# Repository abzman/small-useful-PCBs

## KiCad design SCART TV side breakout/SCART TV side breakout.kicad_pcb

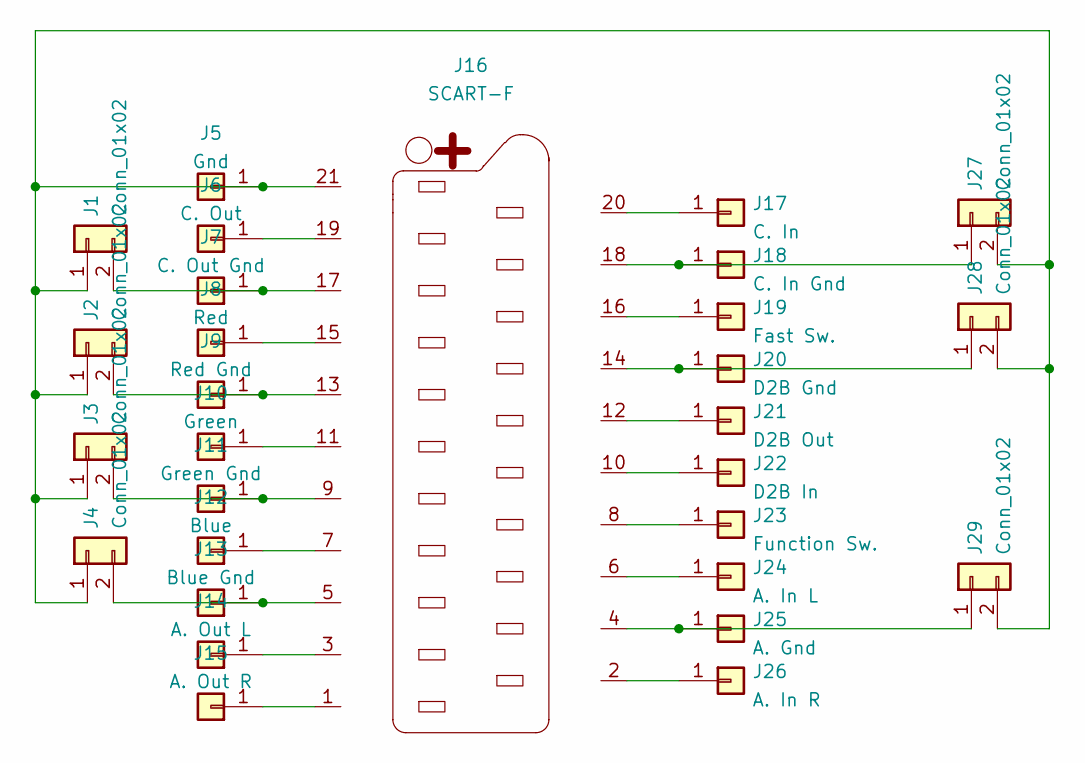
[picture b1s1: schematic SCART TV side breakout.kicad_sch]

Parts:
J1, J2, J3, J4, J27, J28, J29: Conn_01x02; SolderJumper-2_P1.3mm_Open_RoundedPad1.0x1.5mm
J5: Gnd; PinHeader_1x01_P2.54mm_Vertical
J6: C. Out; PinHeader_1x01_P2.54mm_Vertical
J7: C. Out Gnd; PinHeader_1x01_P2.54mm_Vertical
J8: Red; PinHeader_1x01_P2.54mm_Vertical
J9: Red Gnd; PinHeader_1x01_P2.54mm_Vertical
J10: Green; PinHeader_1x01_P2.54mm_Vertical
J11: Green Gnd; PinHeader_1x01_P2.54mm_Vertical
J12: Blue; PinHeader_1x01_P2.54mm_Vertical
J13: Blue Gnd; PinHeader_1x01_P2.54mm_Vertical
J14: A. Out L; PinHeader_1x01_P2.54mm_Vertical
J15: A. Out R; PinHeader_1x01_P2.54mm_Vertical
J16: SCART-F
J17: C. In; PinHeader_1x01_P2.54mm_Vertical
J18: C. In Gnd; PinHeader_1x01_P2.54mm_Vertical
J19: Fast Sw.; PinHeader_1x01_P2.54mm_Vertical
J20: D2B Gnd; PinHeader_1x01_P2.54mm_Vertical
J21: D2B Out; PinHeader_1x01_P2.54mm_Vertical
J22: D2B In; PinHeader_1x01_P2.54mm_Vertical
J23: Function Sw.; PinHeader_1x01_P2.54mm_Vertical
J24: A. In L; PinHeader_1x01_P2.54mm_Vertical
J25: A. Gnd; PinHeader_1x01_P2.54mm_Vertical
J26: A. In R; PinHeader_1x01_P2.54mm_Vertical

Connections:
unnamed: J1.1, J2.1, J3.1, J4.1, J5.1, J16.21, J27.2, J28.2, J29.2
unnamed: J1.2, J7.1, J16.17
unnamed: J10.1, J16.11
unnamed: J3.2, J11.1, J16.9
unnamed: J12.1, J16.7
unnamed: J4.2, J13.1, J16.5
unnamed: J14.1, J16.3
unnamed: J15.1, J16.1
unnamed: J16.2, J26.1
unnamed: J16.4, J25.1, J29.1
unnamed: J16.6, J24.1
unnamed: J16.8, J23.1
unnamed: J16.10, J22.1
unnamed: J16.12, J21.1
unnamed: J2.2, J9.1, J16.13
unnamed: J16.14, J20.1, J28.1
unnamed: J8.1, J16.15
unnamed: J16.16, J19.1
unnamed: J16.18, J18.1, J27.1
unnamed: J6.1, J16.19
unnamed: J16.20, J17.1

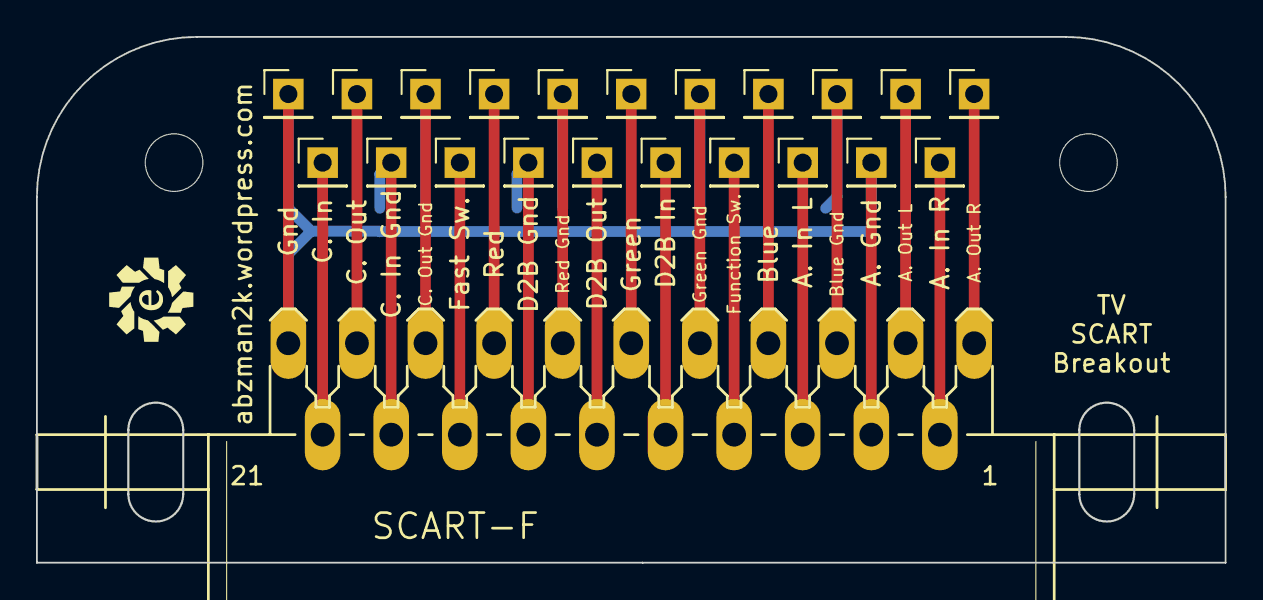
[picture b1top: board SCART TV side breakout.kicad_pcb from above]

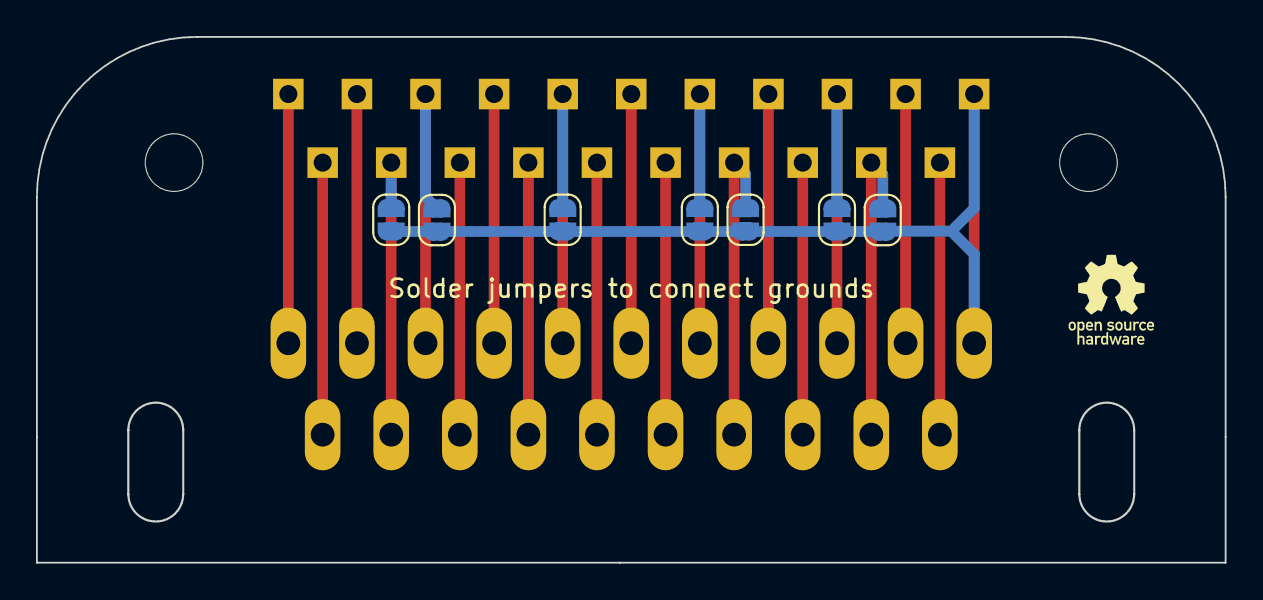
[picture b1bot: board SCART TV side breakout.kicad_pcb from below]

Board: 2 copper layers, 66.0 x 29.2 mm, 29 parts (7 on the bottom side), 21 nets.

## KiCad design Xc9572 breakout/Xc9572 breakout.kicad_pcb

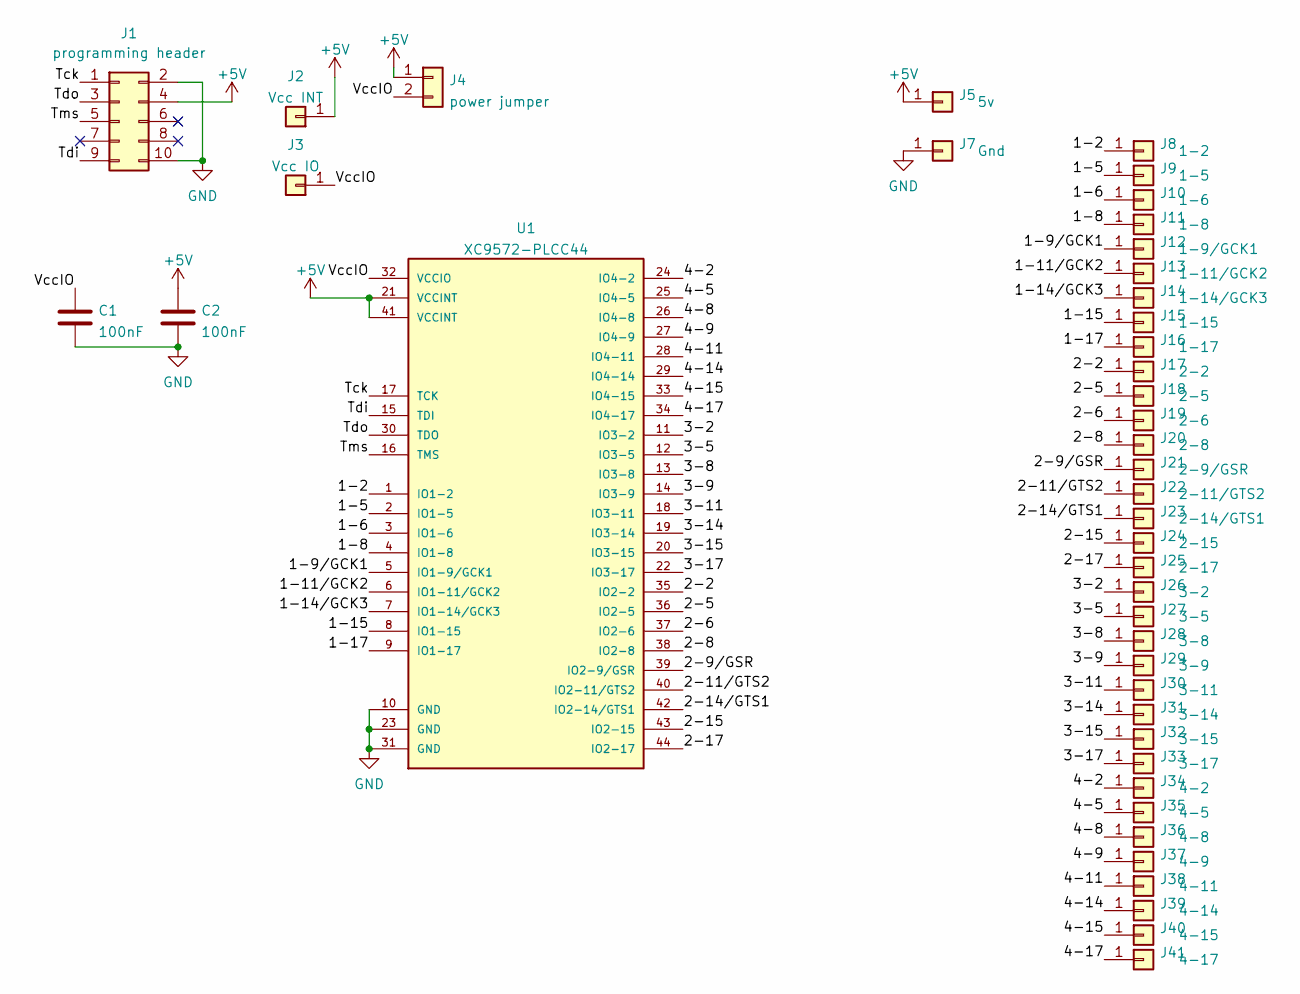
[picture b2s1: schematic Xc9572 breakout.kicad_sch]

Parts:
C1, C2: 100nF; C_0603_1608Metric
J1: programming header; PinHeader_2x05_P2.54mm_Vertical
J2: Vcc INT; PinHeader_1x01_P2.54mm_Vertical
J3: Vcc IO; PinHeader_1x01_P2.54mm_Vertical
J4: power jumper; PinHeader_1x02_P2.54mm_Vertical
J5: 5v; PinHeader_1x01_P2.54mm_Vertical
J7: Gnd; PinHeader_1x01_P2.54mm_Vertical
J8: 1-2; PinHeader_1x01_P2.54mm_Vertical
J9: 1-5; PinHeader_1x01_P2.54mm_Vertical
J10: 1-6; PinHeader_1x01_P2.54mm_Vertical
J11: 1-8; PinHeader_1x01_P2.54mm_Vertical
J12: 1-9/GCK1; PinHeader_1x01_P2.54mm_Vertical
J13: 1-11/GCK2; PinHeader_1x01_P2.54mm_Vertical
J14: 1-14/GCK3; PinHeader_1x01_P2.54mm_Vertical
J15: 1-15; PinHeader_1x01_P2.54mm_Vertical
J16: 1-17; PinHeader_1x01_P2.54mm_Vertical
J17: 2-2; PinHeader_1x01_P2.54mm_Vertical
J18: 2-5; PinHeader_1x01_P2.54mm_Vertical
J19: 2-6; PinHeader_1x01_P2.54mm_Vertical
J20: 2-8; PinHeader_1x01_P2.54mm_Vertical
J21: 2-9/GSR; PinHeader_1x01_P2.54mm_Vertical
J22: 2-11/GTS2; PinHeader_1x01_P2.54mm_Vertical
J23: 2-14/GTS1; PinHeader_1x01_P2.54mm_Vertical
J24: 2-15; PinHeader_1x01_P2.54mm_Vertical
J25: 2-17; PinHeader_1x01_P2.54mm_Vertical
J26: 3-2; PinHeader_1x01_P2.54mm_Vertical
J27: 3-5; PinHeader_1x01_P2.54mm_Vertical
J28: 3-8; PinHeader_1x01_P2.54mm_Vertical
J29: 3-9; PinHeader_1x01_P2.54mm_Vertical
J30: 3-11; PinHeader_1x01_P2.54mm_Vertical
J31: 3-14; PinHeader_1x01_P2.54mm_Vertical
J32: 3-15; PinHeader_1x01_P2.54mm_Vertical
J33: 3-17; PinHeader_1x01_P2.54mm_Vertical
J34: 4-2; PinHeader_1x01_P2.54mm_Vertical
J35: 4-5; PinHeader_1x01_P2.54mm_Vertical
J36: 4-8; PinHeader_1x01_P2.54mm_Vertical
J37: 4-9; PinHeader_1x01_P2.54mm_Vertical
J38: 4-11; PinHeader_1x01_P2.54mm_Vertical
J39: 4-14; PinHeader_1x01_P2.54mm_Vertical
J40: 4-15; PinHeader_1x01_P2.54mm_Vertical
J41: 4-17; PinHeader_1x01_P2.54mm_Vertical
U1: XC9572-PLCC44; PLCC-44

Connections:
+5V: C2.1, J1.4, J2.1, J4.1, J5.1, U1.21 (VCCINT), U1.41 (VCCINT)
/1-2: J8.1, U1.1 (IO1-2)
/1-5: J9.1, U1.2 (IO1-5)
/1-6: J10.1, U1.3 (IO1-6)
/1-8: J11.1, U1.4 (IO1-8)
/1-9/GCK1: J12.1, U1.5 (IO1-9/GCK1)
/1-11/GCK2: J13.1, U1.6 (IO1-11/GCK2)
/1-14/GCK3: J14.1, U1.7 (IO1-14/GCK3)
/1-15: J15.1, U1.8 (IO1-15)
/1-17: J16.1, U1.9 (IO1-17)
/2-2: J17.1, U1.35 (IO2-2)
/2-5: J18.1, U1.36 (IO2-5)
/2-6: J19.1, U1.37 (IO2-6)
/2-8: J20.1, U1.38 (IO2-8)
/2-9/GSR: J21.1, U1.39 (IO2-9/GSR)
/2-11/GTS2: J22.1, U1.40 (IO2-11/GTS2)
/2-14/GTS1: J23.1, U1.42 (IO2-14/GTS1)
/2-15: J24.1, U1.43 (IO2-15)
/2-17: J25.1, U1.44 (IO2-17)
/3-2: J26.1, U1.11 (IO3-2)
/3-5: J27.1, U1.12 (IO3-5)
/3-8: J28.1, U1.13 (IO3-8)
/3-9: J29.1, U1.14 (IO3-9)
/3-11: J30.1, U1.18 (IO3-11)
/3-14: J31.1, U1.19 (IO3-14)
/3-15: J32.1, U1.20 (IO3-15)
/3-17: J33.1, U1.22 (IO3-17)
/4-2: J34.1, U1.24 (IO4-2)
/4-5: J35.1, U1.25 (IO4-5)
/4-8: J36.1, U1.26 (IO4-8)
/4-9: J37.1, U1.27 (IO4-9)
/4-11: J38.1, U1.28 (IO4-11)
/4-14: J39.1, U1.29 (IO4-14)
/4-15: J40.1, U1.33 (IO4-15)
/4-17: J41.1, U1.34 (IO4-17)
/Tck: J1.1, U1.17 (TCK)
/Tdi: J1.9, U1.15 (TDI)
/Tdo: J1.3, U1.30 (TDO)
/Tms: J1.5, U1.16 (TMS)
/VccIO: C1.1, J3.1, J4.2, U1.32 (VCCIO)
GND: C1.2, C2.2, J1.2, J1.10, J7.1, U1.10 (GND), U1.23 (GND), U1.31 (GND)

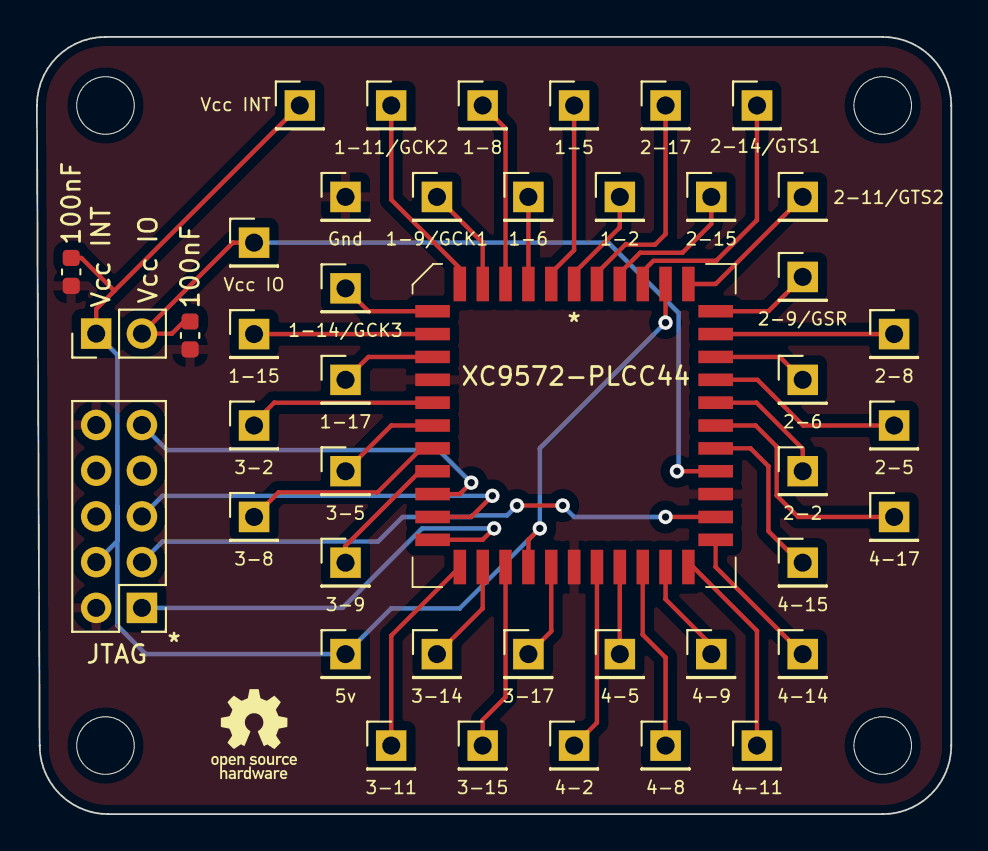
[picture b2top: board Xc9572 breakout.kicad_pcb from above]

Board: 2 copper layers, 50.8 x 43.2 mm, 43 parts (0 on the bottom side), 41 nets.

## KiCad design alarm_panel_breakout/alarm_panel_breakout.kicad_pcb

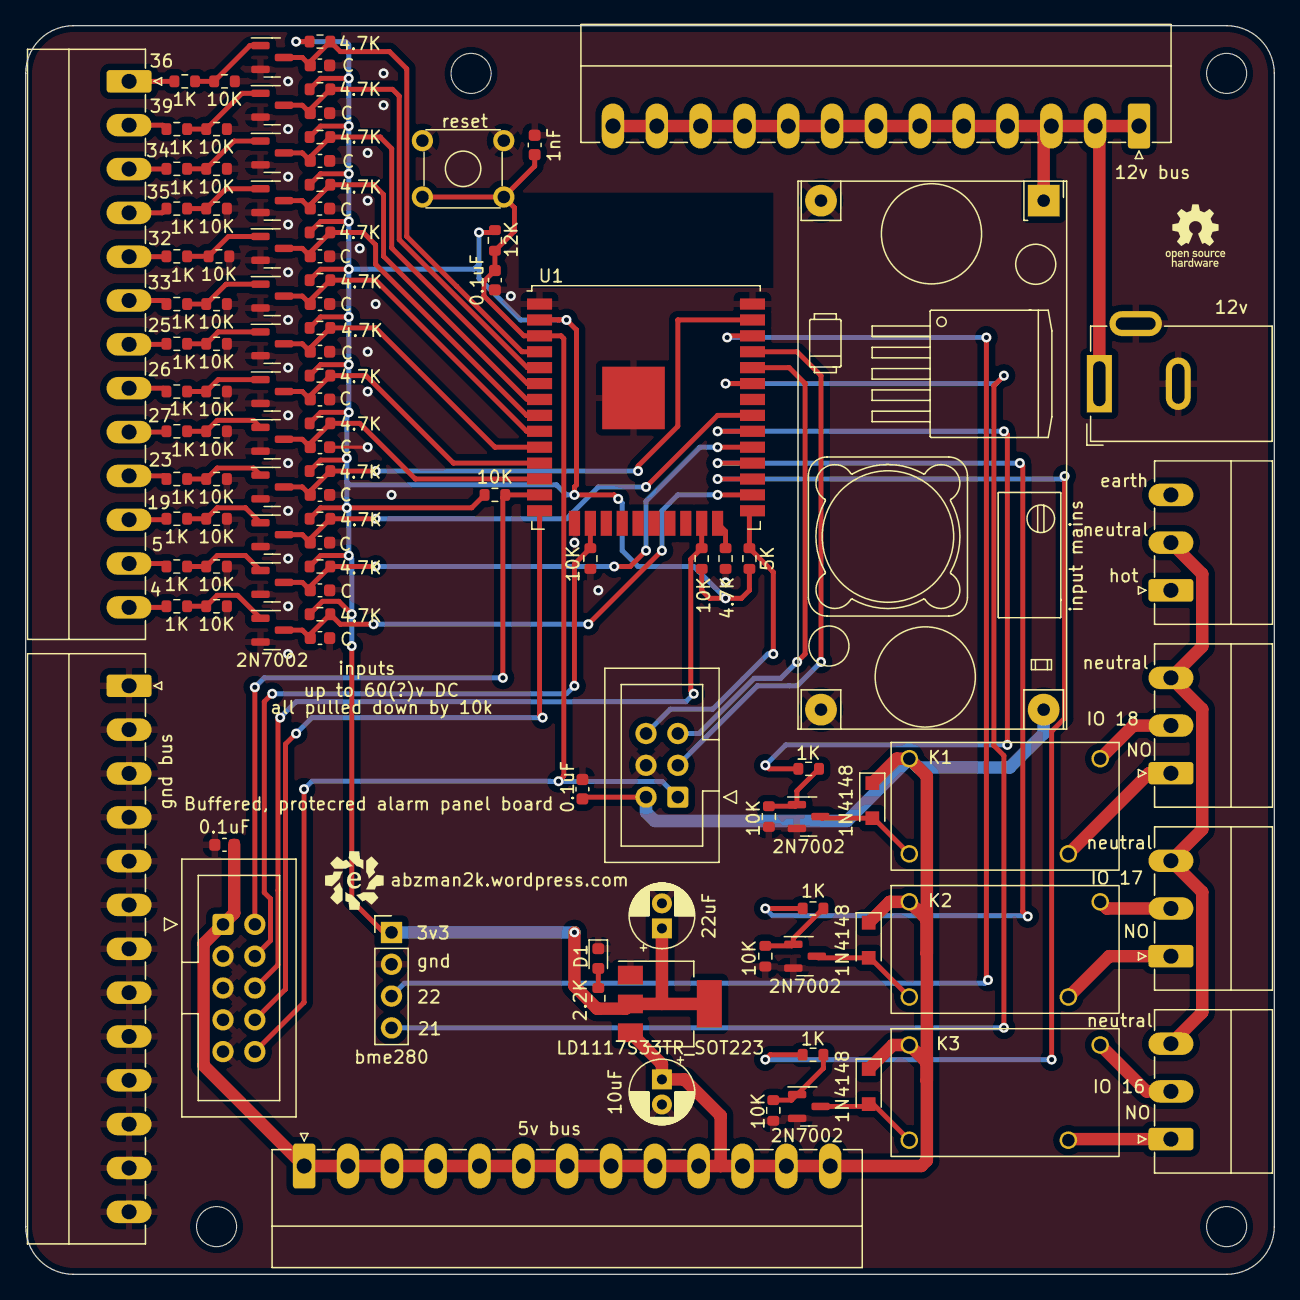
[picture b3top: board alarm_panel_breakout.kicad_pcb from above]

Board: 2 copper layers, 99.7 x 99.7 mm, 110 parts (0 on the bottom side), 71 nets.

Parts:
C1, C3, C6: 0.1uF; C_0603_1608Metric
C2: 1nF; C_0603_1608Metric
C4: 10uF; CP_Radial_D5.0mm_P2.00mm
C5: 22uF; CP_Radial_D5.0mm_P2.00mm
C7, C8, C9, C10, C11, C12, C13, C14, C15, C16, C17, C18, C19: C; C_0603_1608Metric
D1: RED LED; LED_0603_1608Metric
D2, D3, D4: 1N4148; D_SOD-123F
J1: Conn_02x05_Odd_Even; IDC-Header_2x05_P2.54mm_Vertical
J2: Conn_02x03_Odd_Even; IDC-Header_2x03_P2.54mm_Vertical
J3: bme280; PinHeader_1x04_P2.54mm_Vertical
J4: Input Mains; PhoenixContact_MC_1,5_3-G-3.81_1x03_P3.81mm_Horizontal
J6: Relay 1; PhoenixContact_MC_1,5_3-G-3.81_1x03_P3.81mm_Horizontal
J7: Relay 2; PhoenixContact_MC_1,5_3-G-3.81_1x03_P3.81mm_Horizontal
J8: Relay 3; PhoenixContact_MC_1,5_3-G-3.81_1x03_P3.81mm_Horizontal
J9: Barrel_Jack_Switch; BarrelJack_GCT_DCJ200-10-A_Horizontal
J10: 12v bus; PhoenixContact_MC_1,5_13-G-3.5_1x13_P3.50mm_Horizontal
J11: inputs; PhoenixContact_MC_1,5_13-G-3.5_1x13_P3.50mm_Horizontal
J12: 5v bus; PhoenixContact_MC_1,5_13-G-3.5_1x13_P3.50mm_Horizontal
J13: gnd bus; PhoenixContact_MC_1,5_13-G-3.5_1x13_P3.50mm_Horizontal
K1, K2, K3: sonoff_relay; sonoff relay
Q1, Q2, Q3, Q4, Q5, Q6, Q7, Q8, Q9, Q10, Q11, Q12, Q13, Q14, Q15, Q16: 2N7002; SOT-23
R1: 12K; R_0603_1608Metric
R2, R5, R6, R9, R11, R13, R15, R18, R21, R24, R27, R30, R33, R36, R39, R42, R45, R48, R51: 10K; R_0603_1608Metric
R3, R16, R19, R22, R25, R28, R31, R34, R37, R40, R43, R46, R49, R52: 4.7K; R_0603_1608Metric
R4: 2.2K; R_0603_1608Metric
R7: 5K; R_0603_1608Metric
R8, R10, R12, R14, R17, R20, R23, R26, R29, R32, R35, R38, R41, R44, R47, R50: 1K; R_0603_1608Metric
SW1: SW_MEC_5E; SW_TH_Tactile_Omron_B3F-10xx
U1: ESP32-WROOM-32U
U2: LD1117S33TR_SOT223; SOT-223-3_TabPin2
U3: YAAJ_DCDC_StepDown_LM2596

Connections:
+3V3: C5.1, J3.1, R1.1, R2.2, R4.1, R6.2, R7.1, R16.1, R19.1, R22.1, R25.1, R28.1, R31.1, R34.1, R37.1, R40.1, R43.1, R46.1, R49.1, R52.1, U1.2 (VDD), U2.2 (VO)
+5V: C1.1, C4.1, C6.1, D2.1 (K), D3.1 (K), D4.1 (K), J1.1, J2.2, J12.1, J12.2, J12.3, J12.4, J12.5, J12.6, J12.7, J12.8, J12.9, J12.10, J12.11, J12.12, J12.13, K1.1, K2.1, K3.1, U2.3 (VI), U3.4 (Vout)
+12V: J9.1, J10.1, J10.2, J10.3, J10.4, J10.5, J10.6, J10.7, J10.8, J10.9, J10.10, J10.11, J10.12, J10.13, U3.1 (Vin)
/ESP_EN: C2.2, C3.1, J1.10, J2.1, R1.2, SW1.3 (K), SW1.4 (A), U1.3 (EN)
/ESP_IO0: J2.6, R7.2, U1.25 (IO0)
/ESP_IO1: J2.3, U1.35 (TXD0/IO1)
/ESP_IO2: R3.1, U1.24 (IO2)
/ESP_IO3: J2.5, U1.34 (RXD0/IO3)
/ESP_IO4: C7.1, Q4.3 (D), R16.2, U1.26 (IO4)
/ESP_IO5: C8.1, Q5.3 (D), R19.2, U1.29 (IO5)
/ESP_IO12: J1.8, U1.14 (IO12)
/ESP_IO13: J1.4, R5.1, U1.16 (IO13)
/ESP_IO14: J1.2, R2.1, U1.13 (IO14)
/ESP_IO15: J1.6, R6.1, U1.23 (IO15)
/ESP_IO16: R12.1, U1.27 (IO16)
/ESP_IO17: R10.1, U1.28 (IO17)
/ESP_IO18: R8.1, U1.30 (IO18)
/ESP_IO19: C9.1, Q6.3 (D), R22.2, U1.31 (IO19)
/ESP_IO21: J3.4, U1.33 (IO21)
/ESP_IO22: J3.3, U1.36 (IO22)
/ESP_IO23: C10.1, Q7.3 (D), R25.2, U1.37 (IO23)
/ESP_IO25: C12.1, Q9.3 (D), R31.2, U1.10 (IO25)
/ESP_IO26: C18.1, Q15.3 (D), R49.2, U1.11 (IO26)
/ESP_IO27: C11.1, Q8.3 (D), R28.2, U1.12 (IO27)
/ESP_IO32: C14.1, Q11.3 (D), R37.2, U1.8 (IO32)
/ESP_IO33: C13.1, Q10.3 (D), R34.2, U1.9 (IO33)
/ESP_IO34: C16.1, Q13.3 (D), R43.2, U1.6 (IO34)
/ESP_IO35: C15.1, Q12.3 (D), R40.2, U1.7 (IO35)
/ESP_IO36: C17.1, Q14.3 (D), R46.2, U1.4 (SENSOR_VP)
/ESP_IO39: C19.1, Q16.3 (D), R52.2, U1.5 (SENSOR_VN)
/In_4: J11.13, R14.1
/In_5: J11.12, R17.1
/In_19: J11.11, R20.1
/In_23: J11.10, R23.1
/In_25: J11.7, R29.1
/In_26: J11.8, R47.1
/In_27: J11.9, R26.1
/In_32: J11.5, R35.1
/In_33: J11.6, R32.1
/In_34: J11.3, R41.1
/In_35: J11.4, R38.1
/In_36: J11.1, R44.1
/In_39: J11.2, R50.1
/Neutral: J4.2, J6.3, J7.3, J8.3
/Relay1: J6.1, K3.3
/Relay1_2: J6.2, K3.2
/Relay2: J7.1, K2.3
/Relay2_2: J7.2, K2.2
/Relay3: J8.1, K1.3
/Relay3_2: J8.2, K1.2
GND: C1.2, C2.1, C3.2, C4.2, C5.2, C6.2, C7.2, C8.2, C9.2, C10.2, C11.2, C12.2, C13.2, C14.2, C15.2, C16.2, C17.2, C18.2, C19.2, D1.1 (K), J1.3, J1.5, J1.7, J1.9, J2.4, J3.2, J9.2, J9.3, J13.1, J13.2, J13.3, J13.4, J13.5, J13.6, J13.7, J13.8, J13.9, J13.10, J13.11, J13.12, J13.13, Q1.2 (S), Q2.2 (S), Q3.2 (S), Q4.2 (S), Q5.2 (S), Q6.2 (S), Q7.2 (S), Q8.2 (S), Q9.2 (S), Q10.2 (S), Q11.2 (S), Q12.2 (S), Q13.2 (S), Q14.2 (S), Q15.2 (S), Q16.2 (S), R3.2, R5.2, R9.2, R11.2, R13.2, R15.2, R18.2, R21.2, R24.2, R27.2, R30.2, R33.2, R36.2, R39.2, R42.2, R45.2, R48.2, R51.2, SW1.1, SW1.2, U1.1 (GND), U1.15 (GND), U1.38 (GND), U1.39 (GND), U2.1 (GND), U3.2 (GND), U3.3 (GND)
unnamed: D1.2 (A), R4.2
unnamed: D2.2 (A), K1.4, Q1.3 (D)
unnamed: D3.2 (A), K2.4, Q2.3 (D)
unnamed: D4.2 (A), K3.4, Q3.3 (D)
unnamed: Q1.1 (G), R8.2, R9.1
unnamed: Q2.1 (G), R10.2, R11.1
unnamed: Q3.1 (G), R12.2, R13.1
unnamed: Q4.1 (G), R14.2, R15.1
unnamed: Q5.1 (G), R17.2, R18.1
unnamed: Q6.1 (G), R20.2, R21.1
unnamed: Q7.1 (G), R23.2, R24.1
unnamed: Q8.1 (G), R26.2, R27.1
unnamed: Q9.1 (G), R29.2, R30.1
unnamed: Q10.1 (G), R32.2, R33.1
unnamed: Q11.1 (G), R35.2, R36.1
unnamed: Q12.1 (G), R38.2, R39.1
unnamed: Q13.1 (G), R41.2, R42.1
unnamed: Q14.1 (G), R44.2, R45.1
unnamed: Q15.1 (G), R47.2, R48.1
unnamed: Q16.1 (G), R50.2, R51.1

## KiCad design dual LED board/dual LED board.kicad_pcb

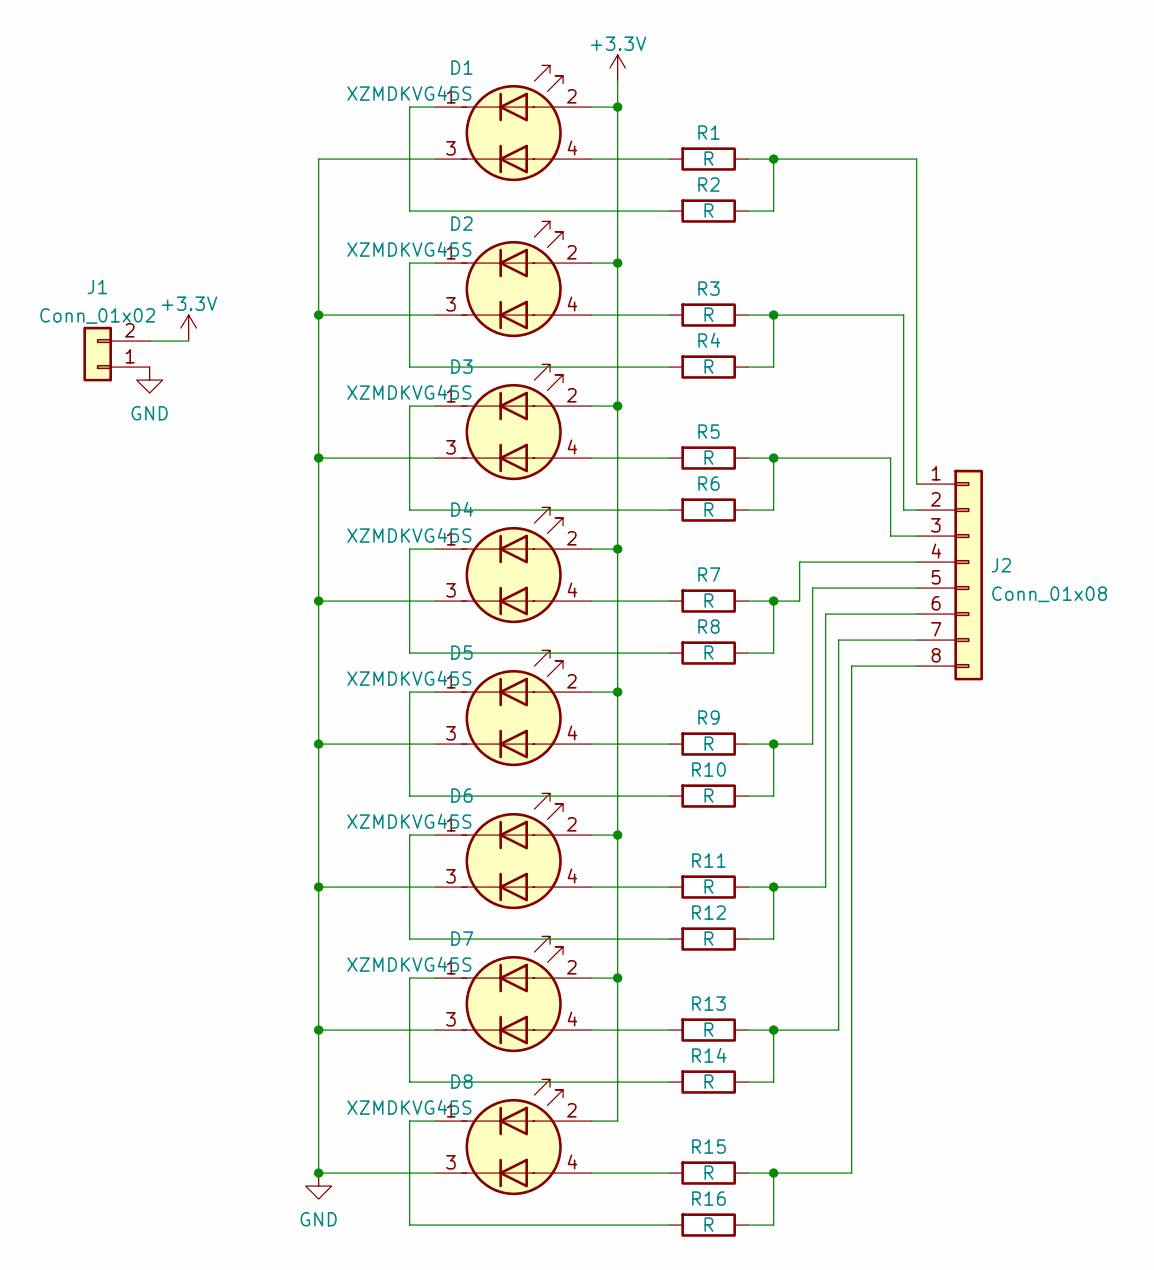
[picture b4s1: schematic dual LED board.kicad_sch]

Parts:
D1, D2, D3, D4, D5, D6, D7, D8: XZMDKVG45S; LED_XZM2CRKM2DGFBB45SCCB
J1: Conn_01x02; PinHeader_1x02_P2.54mm_Vertical
J2: Conn_01x08; PinSocket_1x08_P2.54mm_Vertical
R1, R2, R3, R4, R5, R6, R7, R8, R9, R10, R11, R12, R13, R14, R15, R16: R; R_0603_1608Metric

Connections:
+3V3: D1.2 (K1), D2.2 (K1), D3.2 (K1), D4.2 (K1), D5.2 (K1), D6.2 (K1), D7.2 (K1), D8.2 (K1), J1.2
GND: D1.3 (A2), D2.3 (A2), D3.3 (A2), D4.3 (A2), D5.3 (A2), D6.3 (A2), D7.3 (A2), D8.3 (A2), J1.1
unnamed: D1.1 (A1), R2.2
unnamed: D1.4 (K2), R1.2
unnamed: D2.1 (A1), R4.2
unnamed: D2.4 (K2), R3.2
unnamed: D3.1 (A1), R6.2
unnamed: D3.4 (K2), R5.2
unnamed: D4.1 (A1), R8.2
unnamed: D4.4 (K2), R7.2
unnamed: D5.1 (A1), R10.2
unnamed: D5.4 (K2), R9.2
unnamed: D6.1 (A1), R12.2
unnamed: D6.4 (K2), R11.2
unnamed: D7.1 (A1), R14.2
unnamed: D7.4 (K2), R13.2
unnamed: D8.1 (A1), R16.2
unnamed: D8.4 (K2), R15.2
unnamed: J2.1, R1.1, R2.1
unnamed: J2.2, R3.1, R4.1
unnamed: J2.3, R5.1, R6.1
unnamed: J2.4, R7.1, R8.1
unnamed: J2.5, R9.1, R10.1
unnamed: J2.6, R11.1, R12.1
unnamed: J2.7, R13.1, R14.1
unnamed: J2.8, R15.1, R16.1

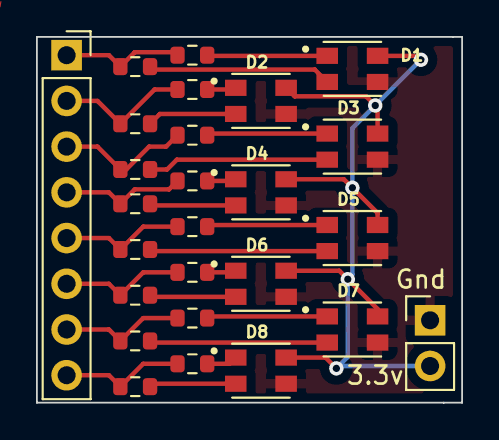
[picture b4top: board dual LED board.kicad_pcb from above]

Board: 2 copper layers, 23.6 x 20.3 mm, 26 parts (0 on the bottom side), 26 nets.

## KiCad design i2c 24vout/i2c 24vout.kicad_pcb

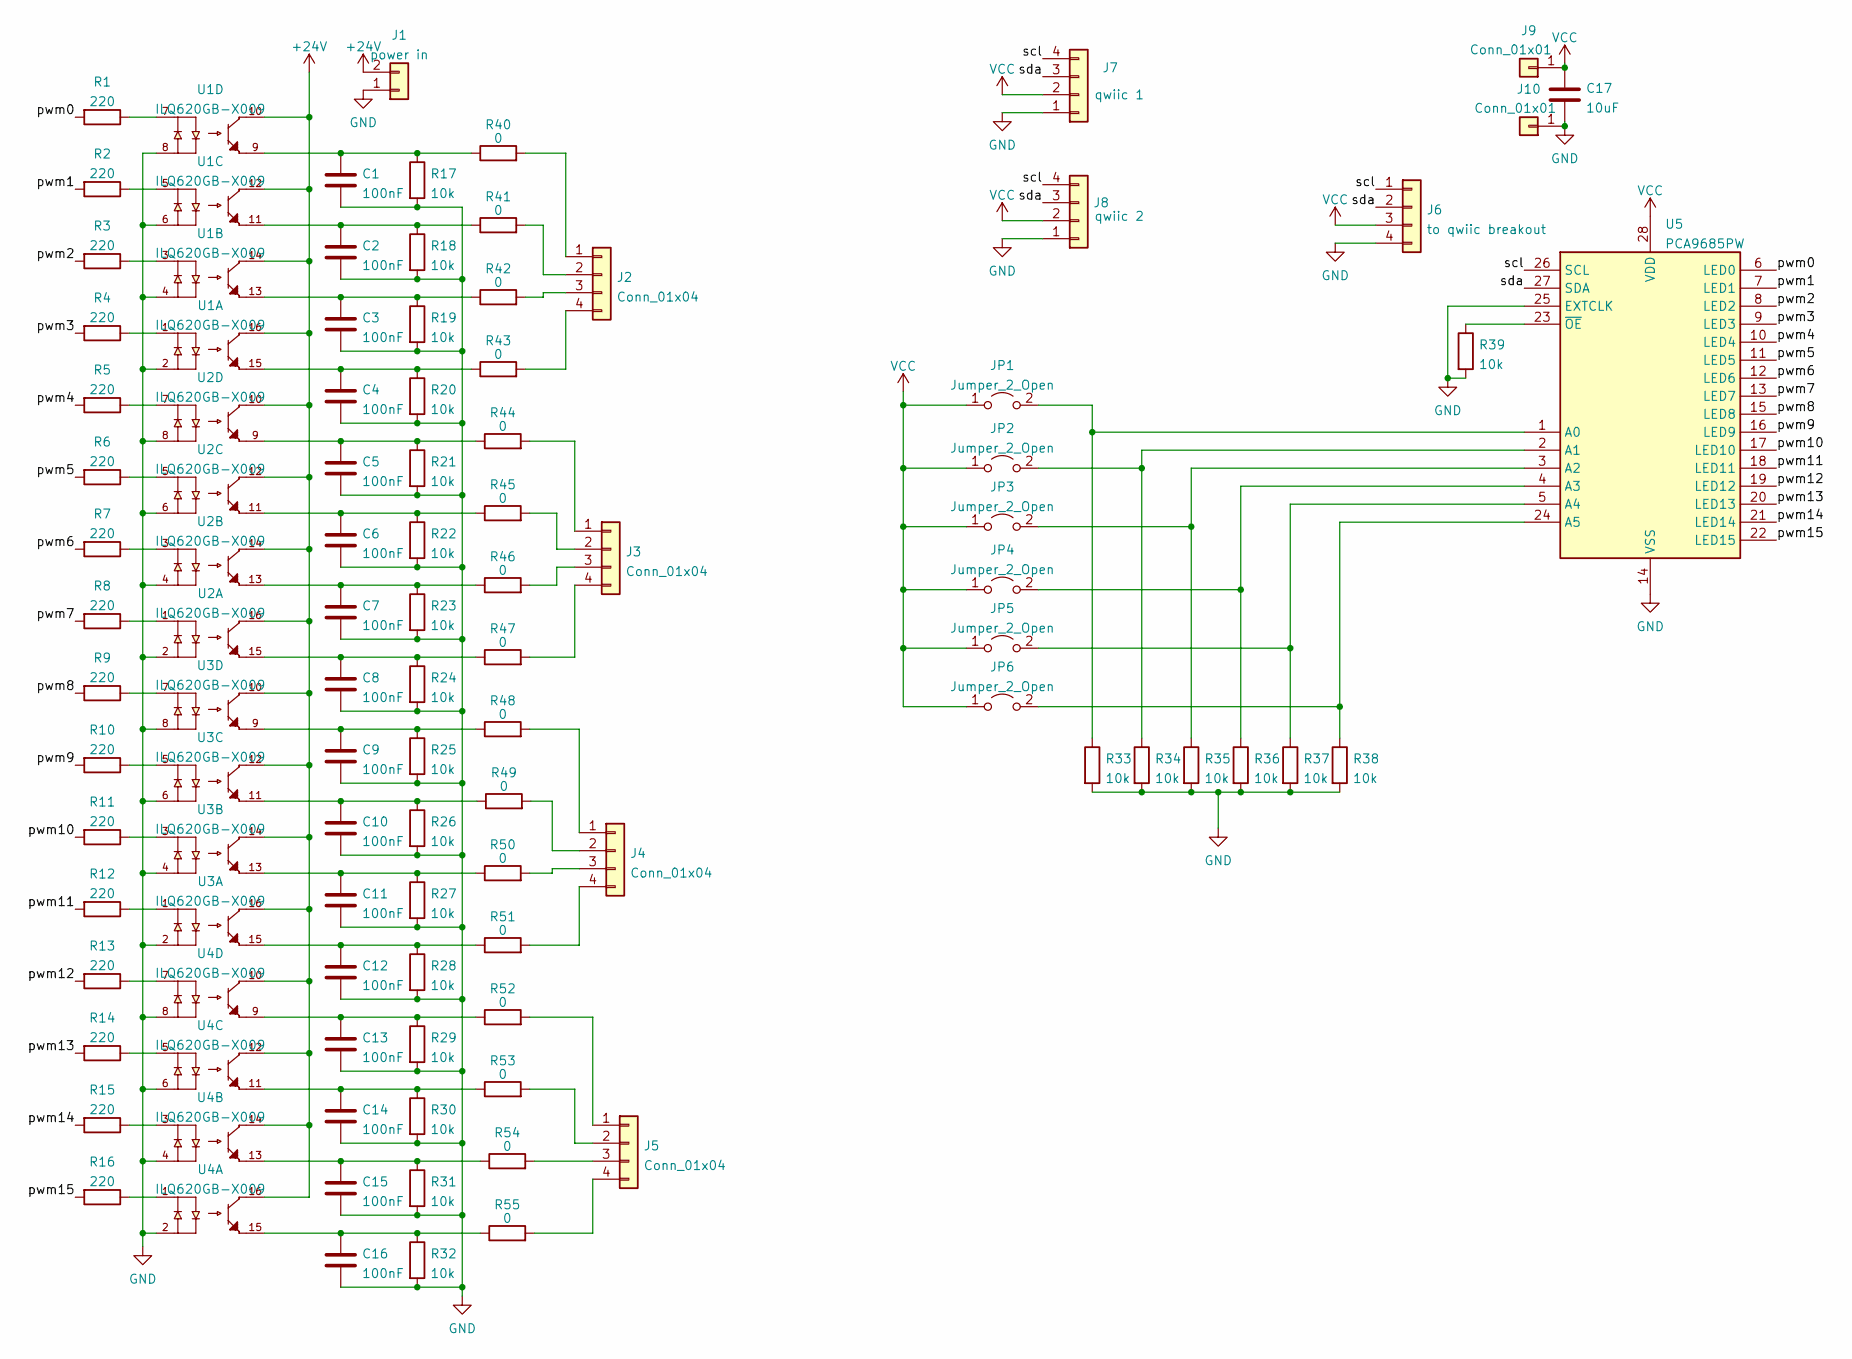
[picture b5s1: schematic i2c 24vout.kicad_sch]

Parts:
C1, C2, C3, C4, C5, C6, C7, C8, C9, C10, C11, C12, C13, C14, C15, C16: 100nF; C_0603_1608Metric
C17: 10uF; C_0603_1608Metric
J1: power in; TerminalBlock_Phoenix_MKDS-1,5-2_1x02_P5.00mm_Horizontal
J2, J3, J4, J5: Conn_01x04; TerminalBlock_Phoenix_MKDS-1,5-4_1x04_P5.00mm_Horizontal
J6: to qwiic breakout; PinHeader_1x04_P2.54mm_Vertical
J7: qwiic 1; JST_SH_SM04B-SRSS-TB_1x04-1MP_P1.00mm_Horizontal
J8: qwiic 2; JST_SH_SM04B-SRSS-TB_1x04-1MP_P1.00mm_Horizontal
J9, J10: Conn_01x01; PinHeader_1x01_P2.54mm_Vertical
JP1, JP2, JP3, JP4, JP5, JP6: Jumper_2_Open; SolderJumper-2_P1.3mm_Open_RoundedPad1.0x1.5mm
R1, R2, R3, R4, R5, R6, R7, R8, R9, R10, R11, R12, R13, R14, R15, R16: 220; R_0603_1608Metric
R17, R18, R19, R20, R21, R22, R23, R24, R25, R26, R27, R28, R29, R30, R31, R32, R33, R34, R35, R36, R37, R38, R39: 10k; R_0603_1608Metric
R40, R41, R42, R43, R44, R45, R46, R47, R48, R49, R50, R51, R52, R53, R54, R55: 0; R_0603_1608Metric
U1, U2, U3, U4: ILQ620GB-X009; OPTO_ILQ620GB-X009; PARTREV 1.8
U5: PCA9685PW; TSSOP-28_4.4x9.7mm_P0.65mm

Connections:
+24V: J1.2, U1.10, U1.12, U1.14, U1.16, U2.10, U2.12, U2.14, U2.16, U3.10, U3.12, U3.14, U3.16, U4.10, U4.12, U4.14, U4.16
/pwm0: R1.2, U5.6 (LED0)
/pwm1: R2.2, U5.7 (LED1)
/pwm2: R3.2, U5.8 (LED2)
/pwm3: R4.2, U5.9 (LED3)
/pwm4: R5.2, U5.10 (LED4)
/pwm5: R6.2, U5.11 (LED5)
/pwm6: R7.2, U5.12 (LED6)
/pwm7: R8.2, U5.13 (LED7)
/pwm8: R9.2, U5.15 (LED8)
/pwm9: R10.2, U5.16 (LED9)
/pwm10: R11.2, U5.17 (LED10)
/pwm11: R12.2, U5.18 (LED11)
/pwm12: R13.2, U5.19 (LED12)
/pwm13: R14.2, U5.20 (LED13)
/pwm14: R15.2, U5.21 (LED14)
/pwm15: R16.2, U5.22 (LED15)
/scl: J6.1, J7.4, J8.4, U5.26 (SCL)
/sda: J6.2, J7.3, J8.3, U5.27 (SDA)
GND: C1.2, C2.2, C3.2, C4.2, C5.2, C6.2, C7.2, C8.2, C9.2, C10.2, C11.2, C12.2, C13.2, C14.2, C15.2, C16.2, C17.2, J1.1, J6.4, J7.1, J7.MP, J8.1, J8.MP, J10.1, R17.2, R18.2, R19.2, R20.2, R21.2, R22.2, R23.2, R24.2, R25.2, R26.2, R27.2, R28.2, R29.2, R30.2, R31.2, R32.2, R33.2, R34.2, R35.2, R36.2, R37.2, R38.2, R39.2, U1.2, U1.4, U1.6, U1.8, U2.2, U2.4, U2.6, U2.8, U3.2, U3.4, U3.6, U3.8, U4.2, U4.4, U4.6, U4.8, U5.14 (VSS), U5.25 (EXTCLK)
unnamed: C1.1, R17.1, R40.1, U1.9
unnamed: C2.1, R18.1, R41.1, U1.11
unnamed: C3.1, R19.1, R42.1, U1.13
unnamed: C4.1, R20.1, R43.1, U1.15
unnamed: C5.1, R21.1, R44.1, U2.9
unnamed: C6.1, R22.1, R45.1, U2.11
unnamed: C7.1, R23.1, R46.1, U2.13
unnamed: C8.1, R24.1, R47.1, U2.15
unnamed: C9.1, R25.1, R48.1, U3.9
unnamed: C10.1, R26.1, R49.1, U3.11
unnamed: C11.1, R27.1, R50.1, U3.13
unnamed: C12.1, R28.1, R51.1, U3.15
unnamed: C13.1, R29.1, R52.1, U4.9
unnamed: C14.1, R30.1, R53.1, U4.11
unnamed: C15.1, R31.1, R54.1, U4.13
unnamed: C16.1, R32.1, R55.1, U4.15
unnamed: J2.1, R40.2
unnamed: J2.2, R41.2
unnamed: J2.3, R42.2
unnamed: J2.4, R43.2
unnamed: J3.1, R44.2
unnamed: J3.2, R45.2
unnamed: J3.3, R46.2
unnamed: J3.4, R47.2
unnamed: J4.1, R48.2
unnamed: J4.2, R49.2
unnamed: J4.3, R50.2
unnamed: J4.4, R51.2
unnamed: J5.1, R52.2
unnamed: J5.2, R53.2
unnamed: J5.3, R54.2
unnamed: J5.4, R55.2
unnamed: JP1.2 (B), R33.1, U5.1 (A0)
unnamed: JP2.2 (B), R34.1, U5.2 (A1)
unnamed: JP3.2 (B), R35.1, U5.3 (A2)
unnamed: JP4.2 (B), R36.1, U5.4 (A3)
unnamed: JP5.2 (B), R37.1, U5.5 (A4)
unnamed: JP6.2 (B), R38.1, U5.24 (A5)
unnamed: R1.1, U1.7
unnamed: R2.1, U1.5
unnamed: R3.1, U1.3
unnamed: R4.1, U1.1
unnamed: R5.1, U2.7
unnamed: R6.1, U2.5
unnamed: R7.1, U2.3
unnamed: R8.1, U2.1
unnamed: R9.1, U3.7
unnamed: R10.1, U3.5
unnamed: R11.1, U3.3
unnamed: R12.1, U3.1
unnamed: R13.1, U4.7
unnamed: R14.1, U4.5
unnamed: R15.1, U4.3
unnamed: R16.1, U4.1
unnamed: R39.1, U5.23 (~OE)
VCC: C17.1, J6.3, J7.2, J8.2, J9.1, JP1.1 (A), JP2.1 (A), JP3.1 (A), JP4.1 (A), JP5.1 (A), JP6.1 (A), U5.28 (VDD)

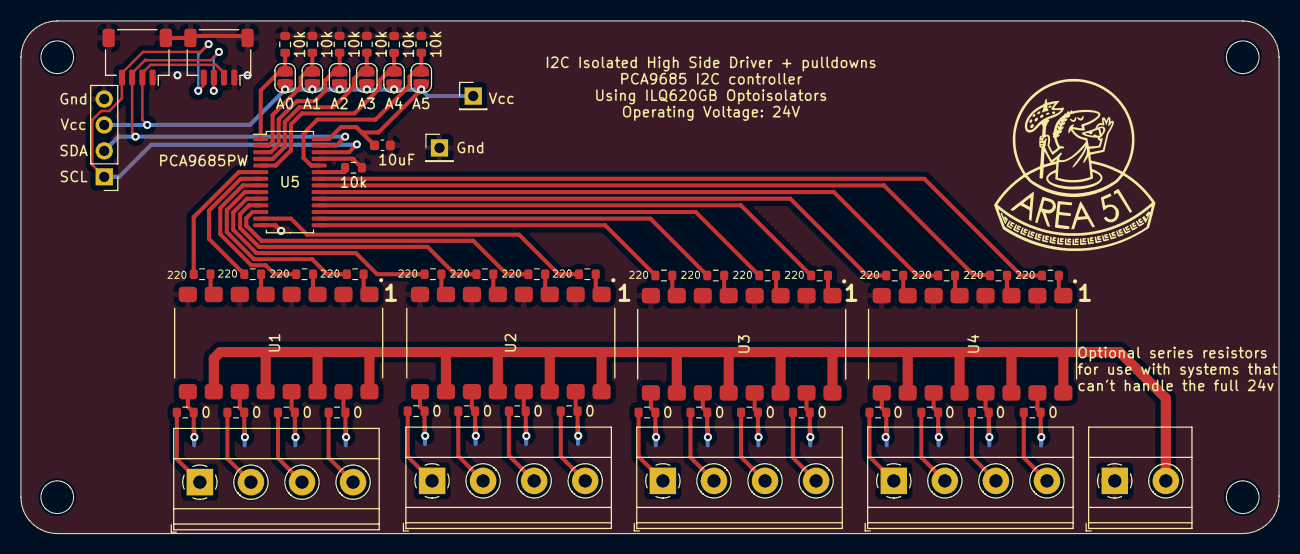
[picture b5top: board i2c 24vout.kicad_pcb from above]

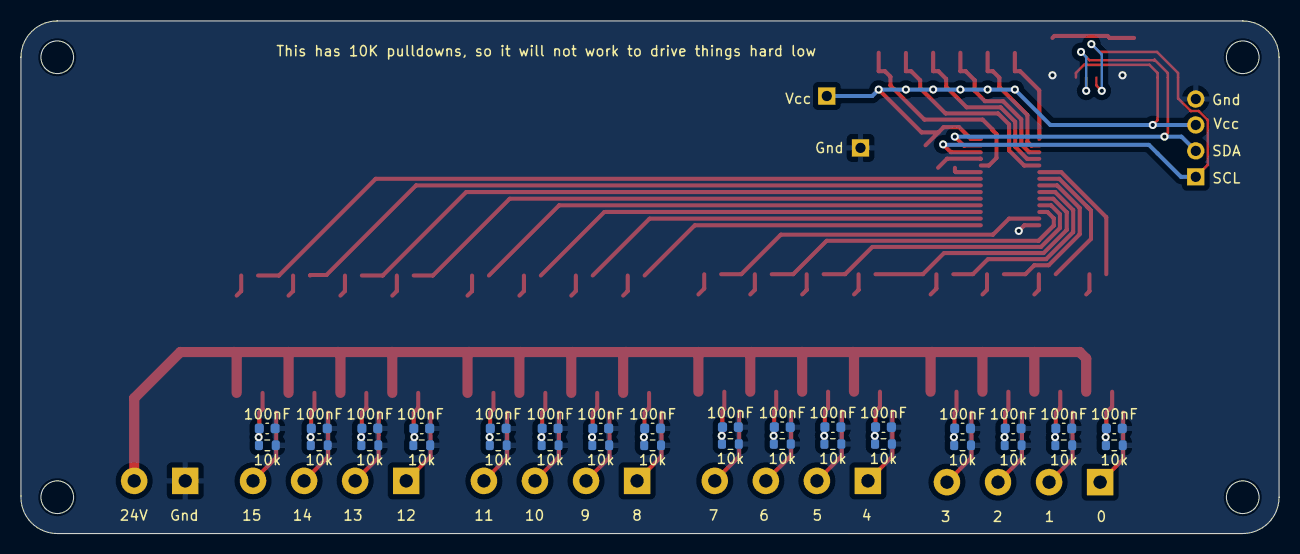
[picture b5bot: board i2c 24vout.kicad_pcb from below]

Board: 2 copper layers, 123.2 x 50.2 mm, 93 parts (32 on the bottom side), 76 nets.
